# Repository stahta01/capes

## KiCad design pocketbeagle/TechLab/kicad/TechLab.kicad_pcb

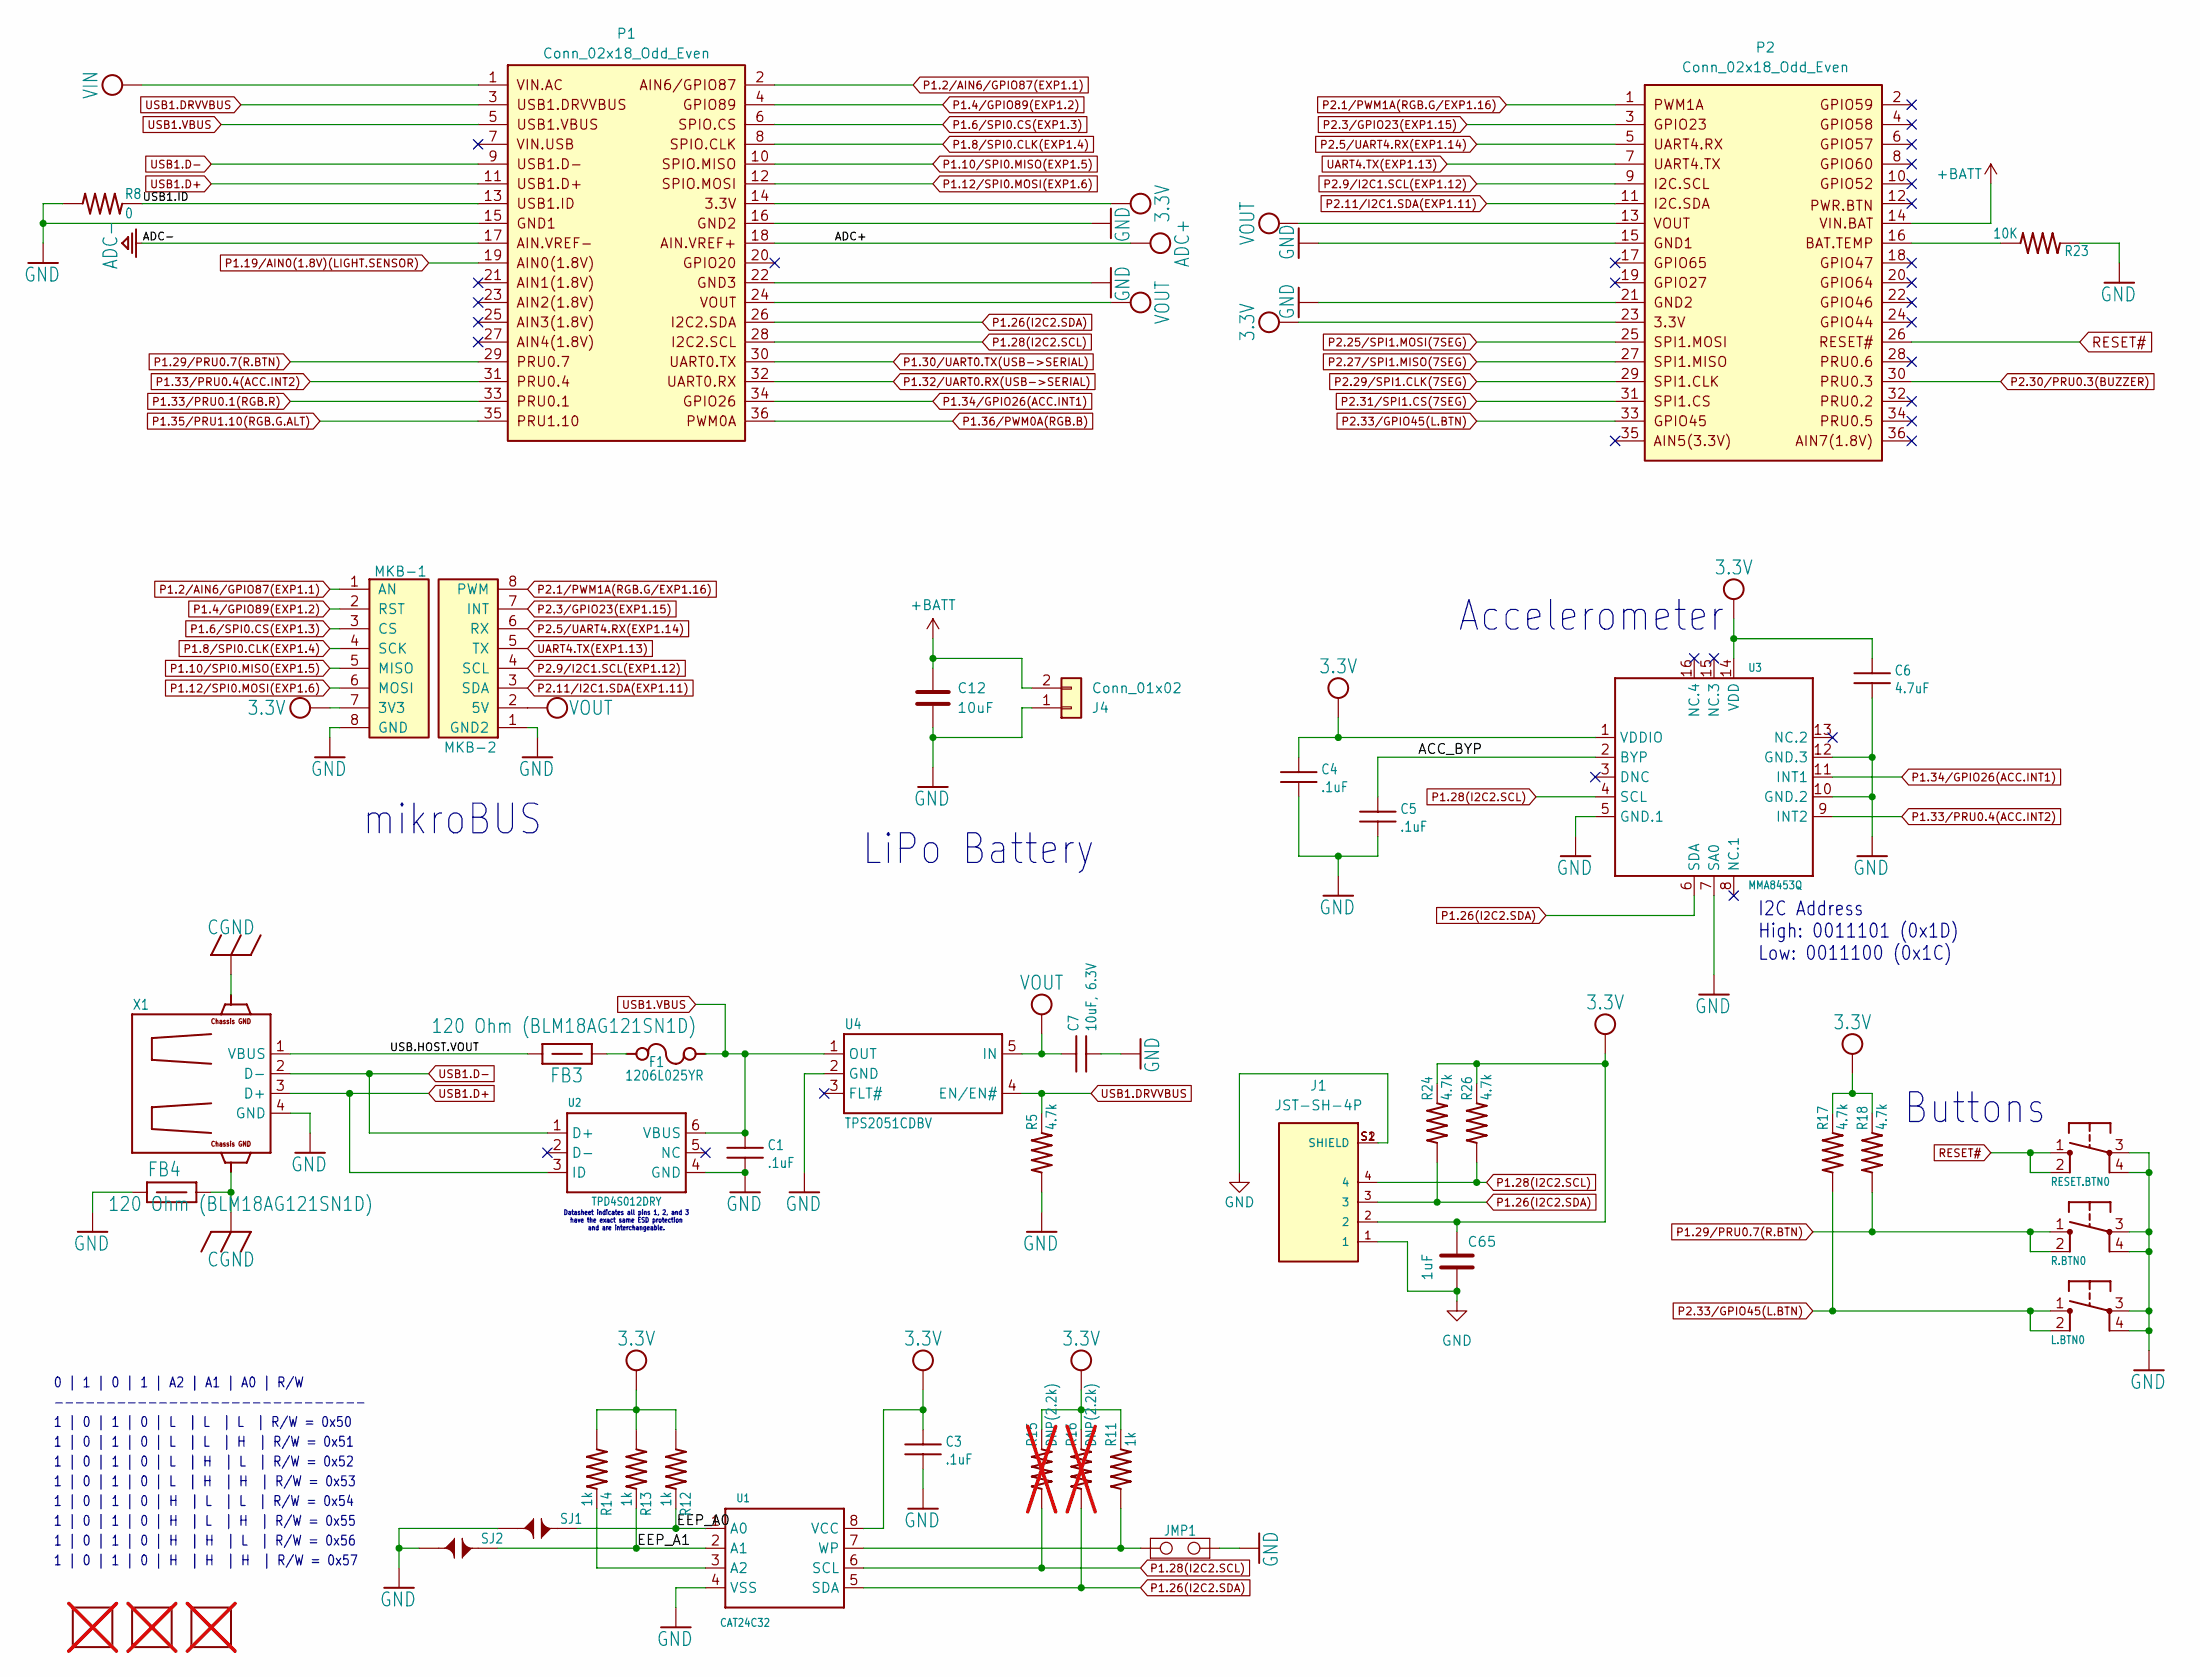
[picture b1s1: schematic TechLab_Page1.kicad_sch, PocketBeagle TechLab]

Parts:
C1, C3, C4, C5: .1uF; 0402; MPN C1005X7R1H104K050BB
C6: 4.7uF; 0402; MPN C1005X5R1A475M050BC
C7: 10uF, 6.3V; 0805; MPN CC0805KKX5R5BB106
C12: 10uF; C_0603_1608Metric
C65: 1uF; C_0603_1608Metric_Pad1.08x0.95mm_HandSolder
F1: 1206L025YR; 1206; MPN 1206L025YR
FB3, FB4: 120 Ohm (BLM18AG121SN1D); 0603; MPN BLM18AG121SN1D
FUD1, FUD2, FUD3: FIDUCIAL; FIDUCIAL_40MIL; not fitted
J1: JST-SH-4P
J4: Conn_01x02; BAT_JST_PH
JMP1: JUMPER-(X2)
L.BTN0: TACTILE.SWITCH-6MM; 6MM_TACTILE-SWITCH; MPN 1301.9315.24
MKB-1, MKB-2: Conn_01x08; PinSocket_1x08_P2.54mm_Vertical_SMD_Pin1Right; MPN SSM-108-L-SV
P1, P2: Conn_02x18_Odd_Even; PinHeader_2x18_P2.54mm_Vertical_SMD; MPN 61003621121
R5, R17, R18, R24, R26: 4.7k; 0402; MPN CRG0402F4K7
R8: 0; 0402; MPN RC0402JR-070RL
R11, R12, R13, R14: 1k; 0402; MPN 1-1622826-8
R15, R16: DNP(2.2k); 0402; not fitted
R23: 10K; 0402; MPN RC0402FR-075K1L
R.BTN0: TACTILE.SWITCH-6MM; 6MM_TACTILE-SWITCH; MPN 1301.9315.24
RESET.BTN0: TACTILE.SWITCH-3X3.5MM; 3X3.5MM-TACTILE-SWITCH; MPN TS23-46-06-BK-160-SMT-TR
SJ1, SJ2: SOLDER.JOINT-(INCH)-0402; SOLDER.JOINT(0402)
U1: CAT24C32; UDFN8,2X3(ON-SEMI); MPN CAT24C32HU4I-GT3
U2: TPD4S012DRY; SON-6(TI)-DRY; MPN TPD4S012DRYR
U3: MMA8453Q; QFN-16-(MMA8453Q); MPN MMA8491QR1
U4: TPS2051CDBV; SOT23-5(TI-DBV); MPN TPS2051CDBVR
X1: 292303-1; MPN 292303-1

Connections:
3.3V: C3.1, C4.1, C6.1, C65.1, J1.2, MKB-1.7 (3V3), P1.14, P2.23, R11.2, R12.1, R13.1, R14.1, R15.2, R16.2, R17.2, R18.2, R24.2, R26.2, U1.8 (VCC), U3.1 (VDDIO), U3.14 (VDD); also elsewhere on the board
+BATT: C12.1, J4.2, P2.14
/Page1/ACC_BYP: C5.1, U3.2 (BYP)
/Page1/EEP_A0: R12.2, SJ1.2, U1.1 (A0)
/Page1/EEP_A1: R13.2, SJ2.2, U1.2 (A1)
/Page1/USB1.ID: P1.13, R8.2
/Page1/USB.HOST.VOUT: FB3.1, X1.1 (VBUS)
ADC+: P1.18; also elsewhere on the board
ADC-: P1.17; also elsewhere on the board
CGND: FB4.2, X1.C1 (CG@6), X1.C2 (CG@5); also elsewhere on the board
GND: C1.2, C3.2, C4.2, C5.2, C6.2, C7.2, C12.2, C65.2, FB4.1, J1.1, J1.S1 (SHIELD), J1.S2 (SHIELD), J4.1, JMP1.2, L.BTN0.3, L.BTN0.4, MKB-1.8 (GND), MKB-2.1 (GND2), P1.15, P1.16, P1.22, P2.15, P2.21, R5.1, R8.1, R23.1, R.BTN0.3, R.BTN0.4, RESET.BTN0.3, RESET.BTN0.4, SJ1.1, SJ2.1, U1.4 (VSS), U2.4 (GND), U3.5 (GND.1), U3.7 (SA0), U3.10 (GND.2), U3.12 (GND.3), U4.2 (GND), X1.4 (GND); also elsewhere on the board
unnamed: F1.1, FB3.2
unnamed: P2.16, R23.2
unnamed: R14.2, U1.3 (A2)
unnamed: JMP1.1, R11.1, U1.7 (WP)
P1.2/AIN6/GPIO87(EXP1.1): MKB-1.1 (AN), P1.2
P1.4/GPIO89(EXP1.2): MKB-1.2 (RST), P1.4
P1.6/SPI0.CS(EXP1.3): MKB-1.3 (CS), P1.6
P1.8/SPI0.CLK(EXP1.4): MKB-1.4 (SCK), P1.8
P1.10/SPI0.MISO(EXP1.5): MKB-1.5 (MISO), P1.10
P1.12/SPI0.MOSI(EXP1.6): MKB-1.6 (MOSI), P1.12
P1.19/AIN0(1.8V)(LIGHT.SENSOR): P1.19; also elsewhere on the board
P1.26(I2C2.SDA): J1.3, P1.26, R16.1, R24.1, U1.5 (SDA), U3.6 (SDA)
P1.28(I2C2.SCL): J1.4, P1.28, R15.1, R26.1, U1.6 (SCL), U3.4 (SCL)
P1.29/PRU0.7(R.BTN): P1.29, R18.1, R.BTN0.1, R.BTN0.2
P1.30/UART0.TX(USB->SERIAL): P1.30; also elsewhere on the board
P1.32/UART0.RX(USB->SERIAL): P1.32; also elsewhere on the board
P1.33/PRU0.1(RGB.R): P1.33; also elsewhere on the board
P1.33/PRU0.4(ACC.INT2): P1.31, U3.9 (INT2)
P1.34/GPIO26(ACC.INT1): P1.34, U3.11 (INT1)
P1.35/PRU1.10(RGB.G.ALT): P1.35; also elsewhere on the board
P1.36/PWM0A(RGB.B): P1.36; also elsewhere on the board
P2.1/PWM1A(RGB.G/EXP1.16): MKB-2.8 (PWM), P2.1; also elsewhere on the board
P2.3/GPIO23(EXP1.15): MKB-2.7 (INT), P2.3
P2.5/UART4.RX(EXP1.14): MKB-2.6 (RX), P2.5
P2.9/I2C1.SCL(EXP1.12): MKB-2.4 (SCL), P2.9
P2.11/I2C1.SDA(EXP1.11): MKB-2.3 (SDA), P2.11
P2.25/SPI1.MOSI(7SEG): P2.25; also elsewhere on the board
P2.27/SPI1.MISO(7SEG): P2.27; also elsewhere on the board
P2.29/SPI1.CLK(7SEG): P2.29; also elsewhere on the board
P2.30/PRU0.3(BUZZER): P2.30; also elsewhere on the board
P2.31/SPI1.CS(7SEG): P2.31; also elsewhere on the board
P2.33/GPIO45(L.BTN): L.BTN0.1, L.BTN0.2, P2.33, R17.1
RESET#: P2.26, RESET.BTN0.1, RESET.BTN0.2; also elsewhere on the board
UART4.TX(EXP1.13): MKB-2.5 (TX), P2.7
USB1.D+: P1.11, U2.3 (ID), X1.3 (D+)
USB1.D-: P1.9, U2.1 (D+), X1.2 (D-)
USB1.DRVVBUS: P1.3, R5.2, U4.4 (EN/EN#)
USB1.VBUS: C1.1, F1.2, P1.5, U2.6 (VBUS), U4.1 (OUT)
VIN: P1.1; also elsewhere on the board
VOUT: C7.1, MKB-2.2 (5V), P1.24, P2.13, U4.5 (IN); also elsewhere on the board

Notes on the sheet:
Accelerometer
Buttons
1 | 0 | 1 | 0 | H | L | L | R/W = 0x54
1 | 0 | 1 | 0 | L | H | H | R/W = 0x53
1 | 0 | 1 | 0 | H | H | H | R/W = 0x57
LiPo Battery
I2C Address High: 0011101 (0x1D) Low: 0011100 (0x1C)
mikroBUS
1 | 0 | 1 | 0 | H | H | L | R/W = 0x56
1 | 0 | 1 | 0 | H | L | H | R/W = 0x55
0 | 1 | 0 | 1 | A2 | A1 | A0 | R/W
1 | 0 | 1 | 0 | L | L | L | R/W = 0x50
1 | 0 | 1 | 0 | L | L | H | R/W = 0x51
1 | 0 | 1 | 0 | L | H | L | R/W = 0x52
Datasheet indicates all pins 1, 2, and 3 have the exact same ESD protection and are interchangeable.
------------------------------

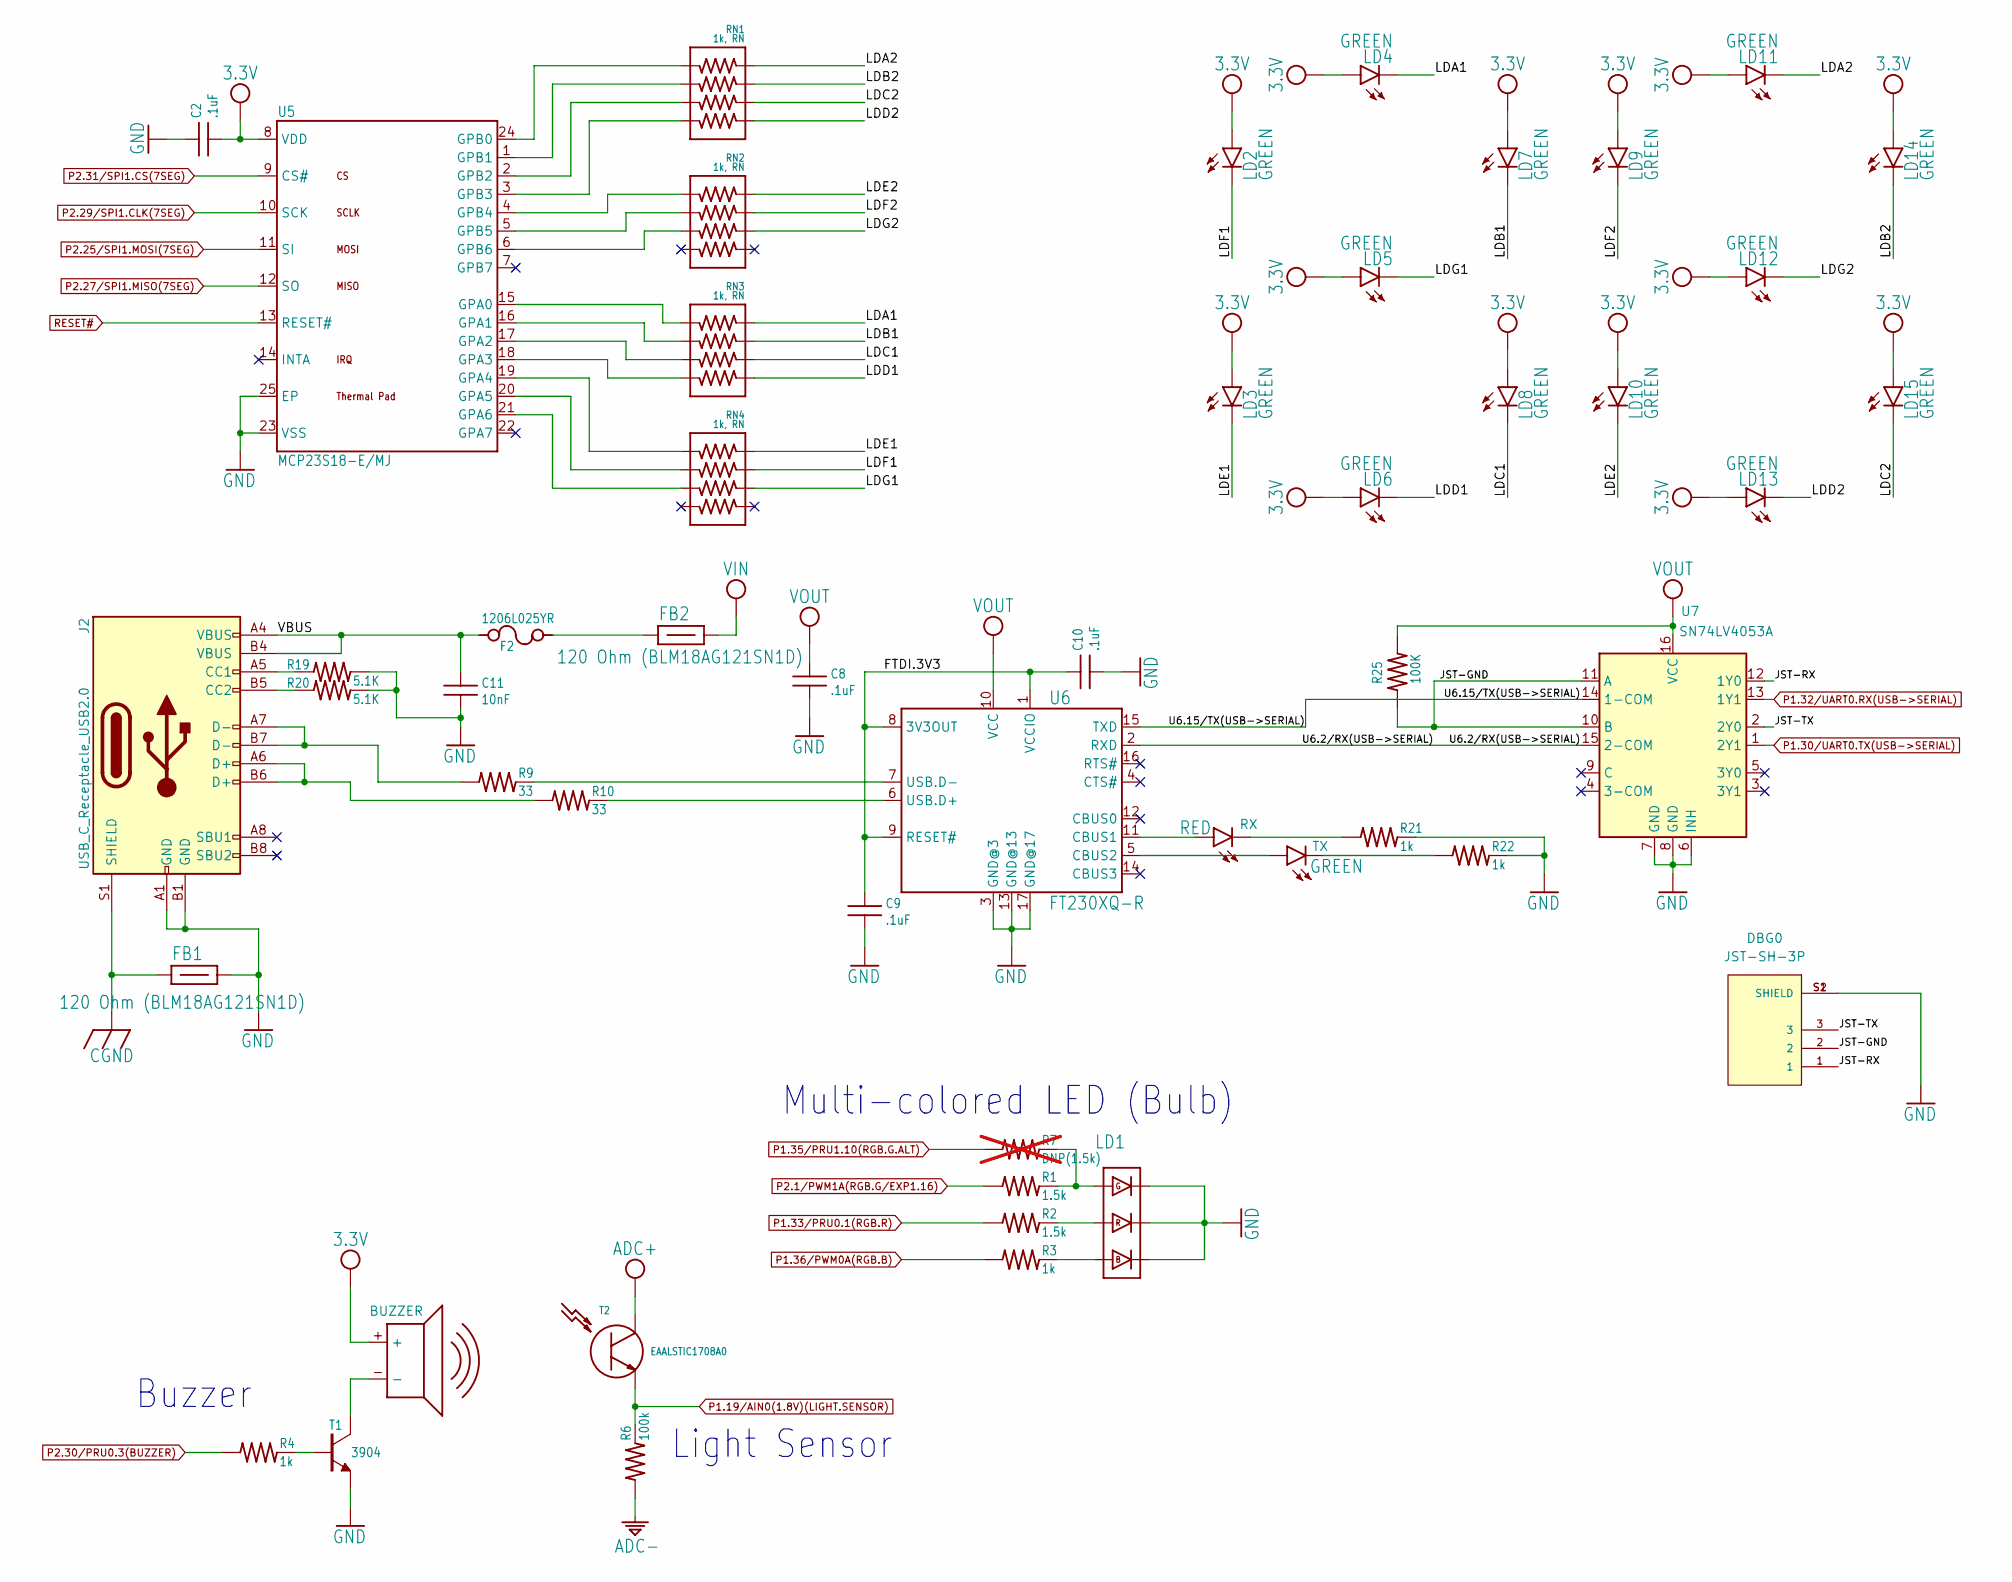
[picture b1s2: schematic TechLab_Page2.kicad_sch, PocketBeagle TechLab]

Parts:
BUZZER0: SMD-140035H; MPN SMT-1427-S-5V-HT-R
C2, C8, C9, C10: .1uF; 0402; MPN C1005X7R1H104K050BB
C11: 10nF; 0402; MPN GCM155R71H103KA55D
DBG0: JST-SH-3P; MPN SM03B-SRSS-TB
F2: 1206L025YR; 1206; MPN 1206L025YR
FB1, FB2: 120 Ohm (BLM18AG121SN1D); 0603; MPN BLM18AG121SN1D
J2: USB_C_Receptacle_USB2.0; USB_C_Receptacle_GCT_USB4105-xx-A_16P_TopMnt_Horizontal; MPN USB4105-GF-A
LD1: JNS-5050RGB; LED_RGB_5050; MPN SMD-LX5050RGB-TR
LD2, LD3, LD4, LD5, LD6, LD7, LD8, LD9, LD10, LD11, LD12, LD13, LD14, LD15: GREEN; 0805-LED; MPN SML-LXT0805GW-TR
R1, R2: 1.5k; 0402; MPN CR0402-FX-1501GLF
R3, R4, R21, R22: 1k; 0402; MPN 1-1622826-8
R6: 100k; 0402; MPN CRG0402F100K
R7: DNP(1.5k); 0402; not fitted
R9, R10: 33; 0402; MPN CR0402-FX-1501GLF
R19, R20: 5.1K; 0402; MPN RC0402FR-075K1L
R25: 100K; 0402; MPN CRG0402F100K
RN1, RN2, RN3, RN4: 1k, RN; RN0804; MPN CAY10-102J4LF
RX0: RED; 0805-LED; MPN 598-8110-107F
T1: 3904; SOT23; MPN MMBT3904-TP
T2: EAALSTIC1708A0; MPN IN-S63DTLS
TX0: GREEN; 0805-LED; MPN SML-LXT0805GW-TR
U5: MCP23S18-E/MJ; QFN24-MJ-0.5-4X4MM; MPN MCP23S18-E/MJ
U6: FT230XQ-R; QFN16-0.65-4X4MM; MPN FT230XQ-R
U7: SN74LV4053A; SOT-23-THN-16; MPN SN74LV4053ADYYR

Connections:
3.3V: BUZZER0.+, C2.2, LD2.A, LD3.A, LD4.A, LD5.A, LD6.A, LD7.A, LD8.A, LD9.A, LD10.A, LD11.A, LD12.A, LD13.A, LD14.A, LD15.A, U5.8 (VDD); also elsewhere on the board
/Page2/FTDI.3V3: C9.1, C10.1, U6.1 (VCCIO), U6.8 (3V3OUT), U6.9 (RESET#)
/Page2/JST-GND: DBG0.2, R25.1, U7.10 (B), U7.11 (A)
/Page2/JST-RX: DBG0.1, U7.12 (1Y0)
/Page2/JST-TX: DBG0.3, U7.2 (2Y0)
/Page2/LDA1: LD4.K, RN3.1
/Page2/LDA2: LD11.K, RN1.1
/Page2/LDB1: LD7.K, RN3.2
/Page2/LDB2: LD14.K, RN1.2
/Page2/LDC1: LD8.K, RN3.3
/Page2/LDC2: LD15.K, RN1.3
/Page2/LDD1: LD6.K, RN3.4
/Page2/LDD2: LD13.K, RN1.4
/Page2/LDE1: LD3.K, RN4.1
/Page2/LDE2: LD10.K, RN2.1
/Page2/LDF1: LD2.K, RN4.2
/Page2/LDF2: LD9.K, RN2.2
/Page2/LDG1: LD5.K, RN4.3
/Page2/LDG2: LD12.K, RN2.3
/Page2/U6.2/RX(USB->SERIAL): U6.2 (RXD), U7.15 (2-COM)
/Page2/U6.15/TX(USB->SERIAL): U6.15 (TXD), U7.14 (1-COM)
/Page2/VBUS: C11.1, F2.1, J2.A4 (VBUS), J2.B4 (VBUS)
ADC+: T2.1 (C); also elsewhere on the board
ADC-: R6.1; also elsewhere on the board
CGND: FB1.1, J2.S1 (SHIELD); also elsewhere on the board
GND: C2.1, C8.2, C9.2, C10.2, C11.2, DBG0.S1 (SHIELD), DBG0.S2 (SHIELD), FB1.2, J2.A1 (GND), J2.B1 (GND), LD1.4(-), LD1.5(-), LD1.6(-), R19.2, R20.2, R21.2, R22.2, T1.2 (E), U5.23 (VSS), U5.25 (EP), U6.3 (GND@3), U6.13 (GND@13), U6.17 (GND@17), U7.6 (INH), U7.7 (GND), U7.8 (GND); also elsewhere on the board
unnamed: F2.2, FB2.1
unnamed: J2.A5 (CC1), R19.1
unnamed: J2.B5 (CC2), R20.1
unnamed: J2.A6 (D+), J2.B6 (D+), R10.1
unnamed: J2.A7 (D-), J2.B7 (D-), R9.1
unnamed: LD1.1(+), R3.2
unnamed: LD1.2(+), R2.2
unnamed: LD1.3(+), R1.2, R7.2
unnamed: R21.1, RX0.K
unnamed: R22.1, TX0.K
unnamed: R4.2, T1.1 (B)
unnamed: BUZZER0.-, T1.3 (C)
unnamed: RN3.8, U5.15 (GPA0)
unnamed: RN3.7, U5.16 (GPA1)
unnamed: RN3.6, U5.17 (GPA2)
unnamed: RN3.5, U5.18 (GPA3)
unnamed: RN4.8, U5.19 (GPA4)
unnamed: RN4.7, U5.20 (GPA5)
unnamed: RN4.6, U5.21 (GPA6)
unnamed: RN1.8, U5.24 (GPB0)
unnamed: RN1.7, U5.1 (GPB1)
unnamed: RN1.6, U5.2 (GPB2)
unnamed: RN1.5, U5.3 (GPB3)
unnamed: RN2.8, U5.4 (GPB4)
unnamed: RN2.7, U5.5 (GPB5)
unnamed: RN2.6, U5.6 (GPB6)
unnamed: RX0.A, U6.11 (CBUS1)
unnamed: TX0.A, U6.5 (CBUS2)
unnamed: R10.2, U6.6 (USB.D+)
unnamed: R9.2, U6.7 (USB.D-)
P1.19/AIN0(1.8V)(LIGHT.SENSOR): R6.2, T2.2 (E); also elsewhere on the board
P1.30/UART0.TX(USB->SERIAL): U7.1 (2Y1); also elsewhere on the board
P1.32/UART0.RX(USB->SERIAL): U7.13 (1Y1); also elsewhere on the board
P1.33/PRU0.1(RGB.R): R2.1; also elsewhere on the board
P1.35/PRU1.10(RGB.G.ALT): R7.1; also elsewhere on the board
P1.36/PWM0A(RGB.B): R3.1; also elsewhere on the board
P2.1/PWM1A(RGB.G/EXP1.16): R1.1; also elsewhere on the board
P2.25/SPI1.MOSI(7SEG): U5.11 (SI); also elsewhere on the board
P2.27/SPI1.MISO(7SEG): U5.12 (SO); also elsewhere on the board
P2.29/SPI1.CLK(7SEG): U5.10 (SCK); also elsewhere on the board
P2.30/PRU0.3(BUZZER): R4.1; also elsewhere on the board
P2.31/SPI1.CS(7SEG): U5.9 (CS#); also elsewhere on the board
RESET#: U5.13 (RESET#); also elsewhere on the board
VIN: FB2.2; also elsewhere on the board
VOUT: C8.1, R25.2, U6.10 (VCC), U7.16 (VCC); also elsewhere on the board

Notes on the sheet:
Multi-colored LED (Bulb)
Buzzer
Light Sensor

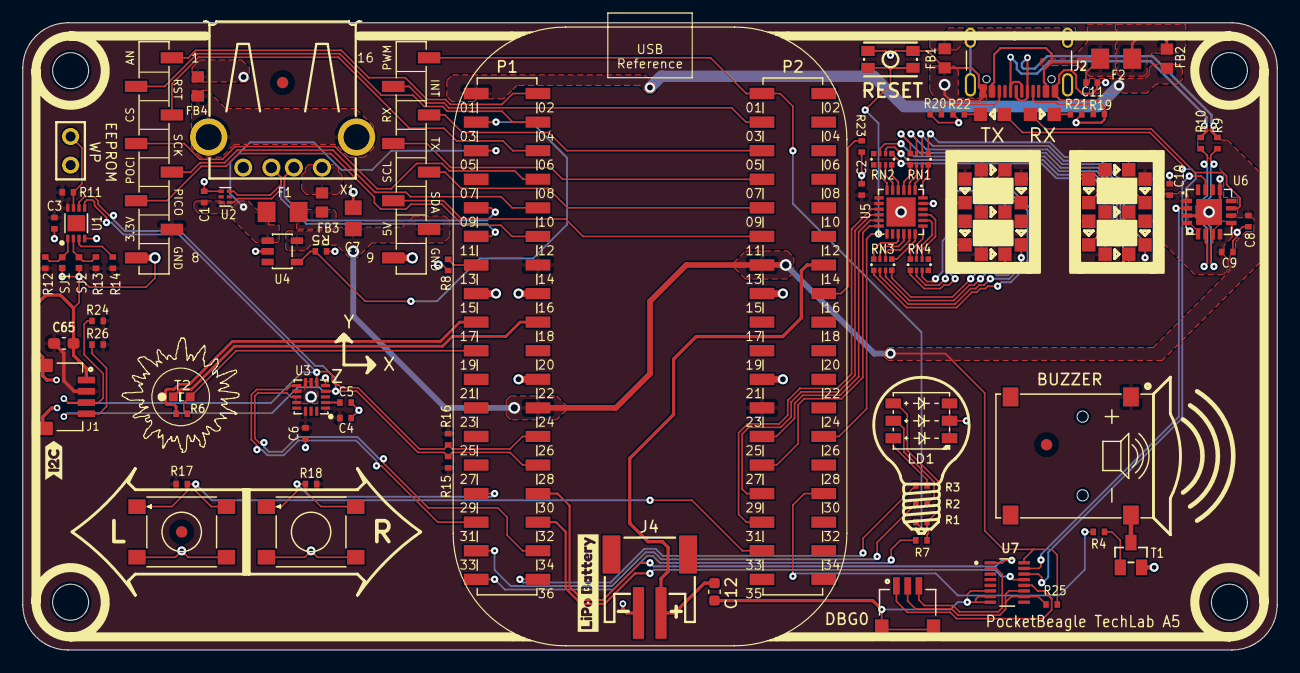
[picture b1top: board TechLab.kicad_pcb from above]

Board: 2 copper layers, 111.5 x 55.8 mm, 100 parts (0 on the bottom side), 102 nets.

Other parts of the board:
@HOLE0, @HOLE1, @HOLE2, @HOLE3: (no value)
kibuzzard-68396DBE: G***; kibuzzard-68396DBE
kibuzzard-68396DE6: G***; kibuzzard-68396DE6

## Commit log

2025-05-27 Update cape header pins slinkscreen front and back
2025-05-30 Add I2C port
2025-05-31 Update cape header pin symbol
2025-05-31 PCB minor updates
2025-05-31 Add Techlab Rev A5 gerbers without logo
